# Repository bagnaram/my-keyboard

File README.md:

# Splendens

**75% keyboard with ISP programmer and USB-C**

**[LICENSE](LICENSE)**

<br />This work is licensed under a <a rel="license" href="http://creativecommons.org/licenses/by-sa/4.0/">Creative Commons Attribution-ShareAlike 4.0 International License</a>.

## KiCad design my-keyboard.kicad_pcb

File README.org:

#+TITLE: Ocotillo Keyboard

* KEYBOARD
60% keyboard with ISP programmer and USB-C

For details on construction please read the assembly blog
[[https://bagnaram.github.io/blog/2020/12/01/keyboard]]

* LICENSE
[[https://i.creativecommons.org/l/by-sa/4.0/88x31.png]]
[[http://creativecommons.org/licenses/by-sa/4.0/][Creative Commons Attribution-ShareAlike 4.0 International License]]

* PHOTOS
[[./doc/ocotillo.png]]
[[./doc/pcb.png]]
[[./doc/pcb-back.png]]

** BOM
I purchased everything from Mouser. Keep in mind these are all SMD components
except for the USB connector and fuse. Therefore, extra care is necessary to
ensure components are properly soldered. Small sensitive components such as the
crystal oscillator cannot endure high temperature of a standard iron. Proceed
with caution.

| Reference                                                                                                                                                                                                                                                                | Quantity | Value                    | Footprint                                      | Datasheet                                                                                                                     | SKU                                       | Quoted Part Number   | Order Quantity | Order Price | Min\Mult Order Qty |
| C1 C2 C3                                                                                                                                                                                                                                                                 |        3 | 0.1uF                    | Capacitor_SMD:C_0805_2012Metric                | Multilayer Ceramic Capacitors MLCC - SMD/SMT Multilayer Ceramic Capacitors MLCC - SMD/SMT .1uF 5% 25V MLCC                    | CC0805JPX7R8BB104                         | 603-CC0805JPX7R8BB10 |              3 | $0.18       | 1\1                |
| C4                                                                                                                                                                                                                                                                       |        1 | 10uF                     | Capacitor_SMD:C_0805_2012Metric                | Multilayer Ceramic Capacitors MLCC - SMD/SMT Multilayer Ceramic Capacitors MLCC - SMD/SMT 0805 25VDC 10uF 10% AEC-Q200        | CGA4J1X7S1E106K125AC                      | 810-CGA4J1X7S1E106K1 |              1 | $0.58       | 1\1                |
| C5 C6                                                                                                                                                                                                                                                                    |        2 | 22pF                     | Capacitor_SMD:C_0805_2012Metric                | Multilayer Ceramic Capacitors MLCC - SMD/SMT Multilayer Ceramic Capacitors MLCC - SMD/SMT 25V 22pF C0G 0805 10% Flex AEC-Q200 | C0805X220K3GACAUTO                        | 80-C0805X220K3GAUTO  |              2 | $0.34       | 1\1                |
| C7                                                                                                                                                                                                                                                                       |        1 | 1uF                      | Capacitor_SMD:C_0805_2012Metric                | Multilayer Ceramic Capacitors MLCC - SMD/SMT Multilayer Ceramic Capacitors MLCC - SMD/SMT 10V 1uF X7R 0805 20% AEC-Q200       | C0805C105M8RACAUTO                        | 80-C0805C105M8RAUTO  |              1 | $0.31       | 1\1                |
| D1 D2 D4 D5 D6 D7 D8 D9 D10 D11 D13 D14 D15 D16 D17 D19 D20 D21 D22 D24 D25 D26 D27 D29 D30 D31 D32 D34 D35 D36 D37 D38 D40 D41 D42 D43 D45 D46 D47 D48 D50 D51 D52 D53 D55 D56 D57 D58 D59 D61 D62 D63 D64 D65 D67 D68 D69 D70 D73 D74 D76 D78 D79 D80 D81 D82 D85      |       67 | D_Small                  | Diode_SMD:D_SOD-123                            | Diodes - General Purpose, Power, Switching Diodes - General Purpose, Power, Switching 100V Io/150mA                           | 1N4148W-E3-08                             | 78-1N4148W-E3-08     |             67 | $0.15       | 1\1                |
| D86 D87                                                                                                                                                                                                                                                                  |        2 | 3.6V                     | Diode_SMD:D_SOD-123                            | Zener Diodes Zener Diodes 3.6V 500mW                                                                                          | MMSZ4685T1G                               | 863-MMSZ4685T1G      |              2 | $0.21       | 1\1                |
| F1                                                                                                                                                                                                                                                                       |        1 | 500mA                    | cftkb:polyfuse_5.1mm                           | Resettable Fuses - PPTC Resettable Fuses - PPTC 60v Max 40Amps Max Hold .50 Trip 1.00                                         | MF-R050                                   | 652-MFR050           |              1 | $0.34       | 1\1                |
| ISP1                                                                                                                                                                                                                                                                     |        1 | AVR-ISP-6                | cftkb:AVR_ICSP_3x2                             | Headers & Wire Housings Headers & Wire Housings 6P DR VRT UNSHRD HDR TIN OVER NICKEL                                          | 68602-406HLF                              | 649-68602-406HLF     |              1 | $0.24       | 1\1                |
| MX0 MX1 MX2 MX3 MX4 MX5 MX6 MX7 MX8 MX9 MX10 MX11 MX12 MX14 MX16 MX17 MX18 MX19 MX20 MX21 MX22 MX23 MX24 MX25 MX26 MX27 MX29 MX31 MX32 MX33 MX34 MX35 MX36 MX37 MX38 MX39 MX40 MX41 MX43 MX45 MX46 MX47 MX48 MX49 MX50 MX51 MX52 MX53 MX54 MX56 MX57 MX63 MX64 MX65 MX66 |       55 | 1                        | MX_Alps_Hybrid:MX-1U-NoLED                     |                                                                                                                               | PCB Mount Gateron Switches (5 Legs) Brown |                      |                |             |                    |
| MX13                                                                                                                                                                                                                                                                     |        1 | 1                        | MX_Alps_Hybrid:MX-2U-NoLED                     |                                                                                                                               | PCB Mount Gateron Switches (5 Legs) Brown |                      |                |             |                    |
| MX15 MX28                                                                                                                                                                                                                                                                |        2 | 1                        | MX_Alps_Hybrid:MX-1.5U-NoLED                   |                                                                                                                               | PCB Mount Gateron Switches (5 Legs) Brown |                      |                |             |                    |
| MX30                                                                                                                                                                                                                                                                     |        1 | 1                        | MX_Alps_Hybrid:MX-1.75U                        |                                                                                                                               | PCB Mount Gateron Switches (5 Legs) Brown |                      |                |             |                    |
| MX42 MX44                                                                                                                                                                                                                                                                |        2 | 1                        | MX_Alps_Hybrid:MX-2.25U-NoLED                  |                                                                                                                               | PCB Mount Gateron Switches (5 Legs) Brown |                      |                |             |                    |
| MX55                                                                                                                                                                                                                                                                     |        1 | 1                        | MX_Alps_Hybrid:MX-1.75U-NoLED                  |                                                                                                                               | PCB Mount Gateron Switches (5 Legs) Brown |                      |                |             |                    |
| MX58 MX59 MX60 MX62                                                                                                                                                                                                                                                      |        4 | 1                        | MX_Alps_Hybrid:MX-1.25U-NoLED                  |                                                                                                                               | PCB Mount Gateron Switches (5 Legs) Brown |                      |                |             |                    |
| MX61                                                                                                                                                                                                                                                                     |        1 | 1                        | MX_Alps_Hybrid:MX-6U-ReversedStabilizers-NoLED |                                                                                                                               | PCB Mount Gateron Switches (5 Legs) Brown |                      |                |             |                    |
| R1 R2                                                                                                                                                                                                                                                                    |        2 | 75                       | Resistor_SMD:R_0805_2012Metric                 | Thick Film Resistors - SMD Thick Film Resistors - SMD 1/8W 75 Ohm 1%                                                          | GWCR0805-75RFT5                           | 756-GWCR0805-75RFT5  |              2 | $0.10       | 1\1                |
| R3 R4                                                                                                                                                                                                                                                                    |        2 | 10k                      | Resistor_SMD:R_0805_2012Metric                 | Thick Film Resistors - SMD Thick Film Resistors - SMD 10K ohm 1% 150V General Purpose SMT                                     | WCR0805-10KFI                             | 756-WCR0805-10KFI    |              2 | $0.10       | 1\1                |
| R5 R6                                                                                                                                                                                                                                                                    |        2 | 5.1k                     | Resistor_SMD:R_0805_2012Metric                 | Thick Film Resistors - SMD Thick Film Resistors - SMD 5.1K 1%                                                                 | CR0805-FX-5101ELF                         | 652-CR0805FX-5101ELF |              2 | $0.10       | 1\1                |
| R7                                                                                                                                                                                                                                                                       |        1 | 1.5k                     | Resistor_SMD:R_0805_2012Metric                 | Thick Film Resistors - SMD Thick Film Resistors - SMD 1.5K 1%                                                                 | CR0805-FX-1501ELF                         | 652-CR0805FX-1501ELF |              1 | $0.10       | 1\1                |
| SW1                                                                                                                                                                                                                                                                      |        1 | SW_Push                  | Random Keyboard Parts:SKQGADE010               | Tactile Switches Tactile Switches 5.2x5.2x1.5mm 260gf                                                                         | SKQGADE010                                | 688-SKQGAD           |              1 | $0.46       | 1\1                |
| U1                                                                                                                                                                                                                                                                       |        1 | ATmega32U4-AU            | Package_QFP:TQFP-44_10x10mm_P0.8mm             | 8-bit Microcontrollers - MCU 8-bit Microcontrollers - MCU AVR USB 32K FLASH INDUSTRIAL                                        | ATmega32U4-AU                             | 556-ATMEGA32U4-AU    |              1 | $4.00       | 1\1                |
| USB1                                                                                                                                                                                                                                                                     |        1 | USB_C_GCT_USB4085-Type-C | cftkb:USB_C_GCT_USB4085                        | USB Connectors USB Connectors USB 3.1 RECE. CONN. Gen 1                                                                       | 10137061-00021LF                          | 649-10137061-00021LF |              1 | $2.24       | 1\1                |
| Y1                                                                                                                                                                                                                                                                       |        1 | 16MHz                    | Crystal:Crystal_SMD_3225-4Pin_3.2x2.5mm        | Crystals Crystals CRYSTAL 16MHZ 8PF SMD                                                                                       | NX3225GA-16.000M-STD-CRG-2                | 344-NX3225GA16MCRG2  |              1 | $0.59       | 1\1                |

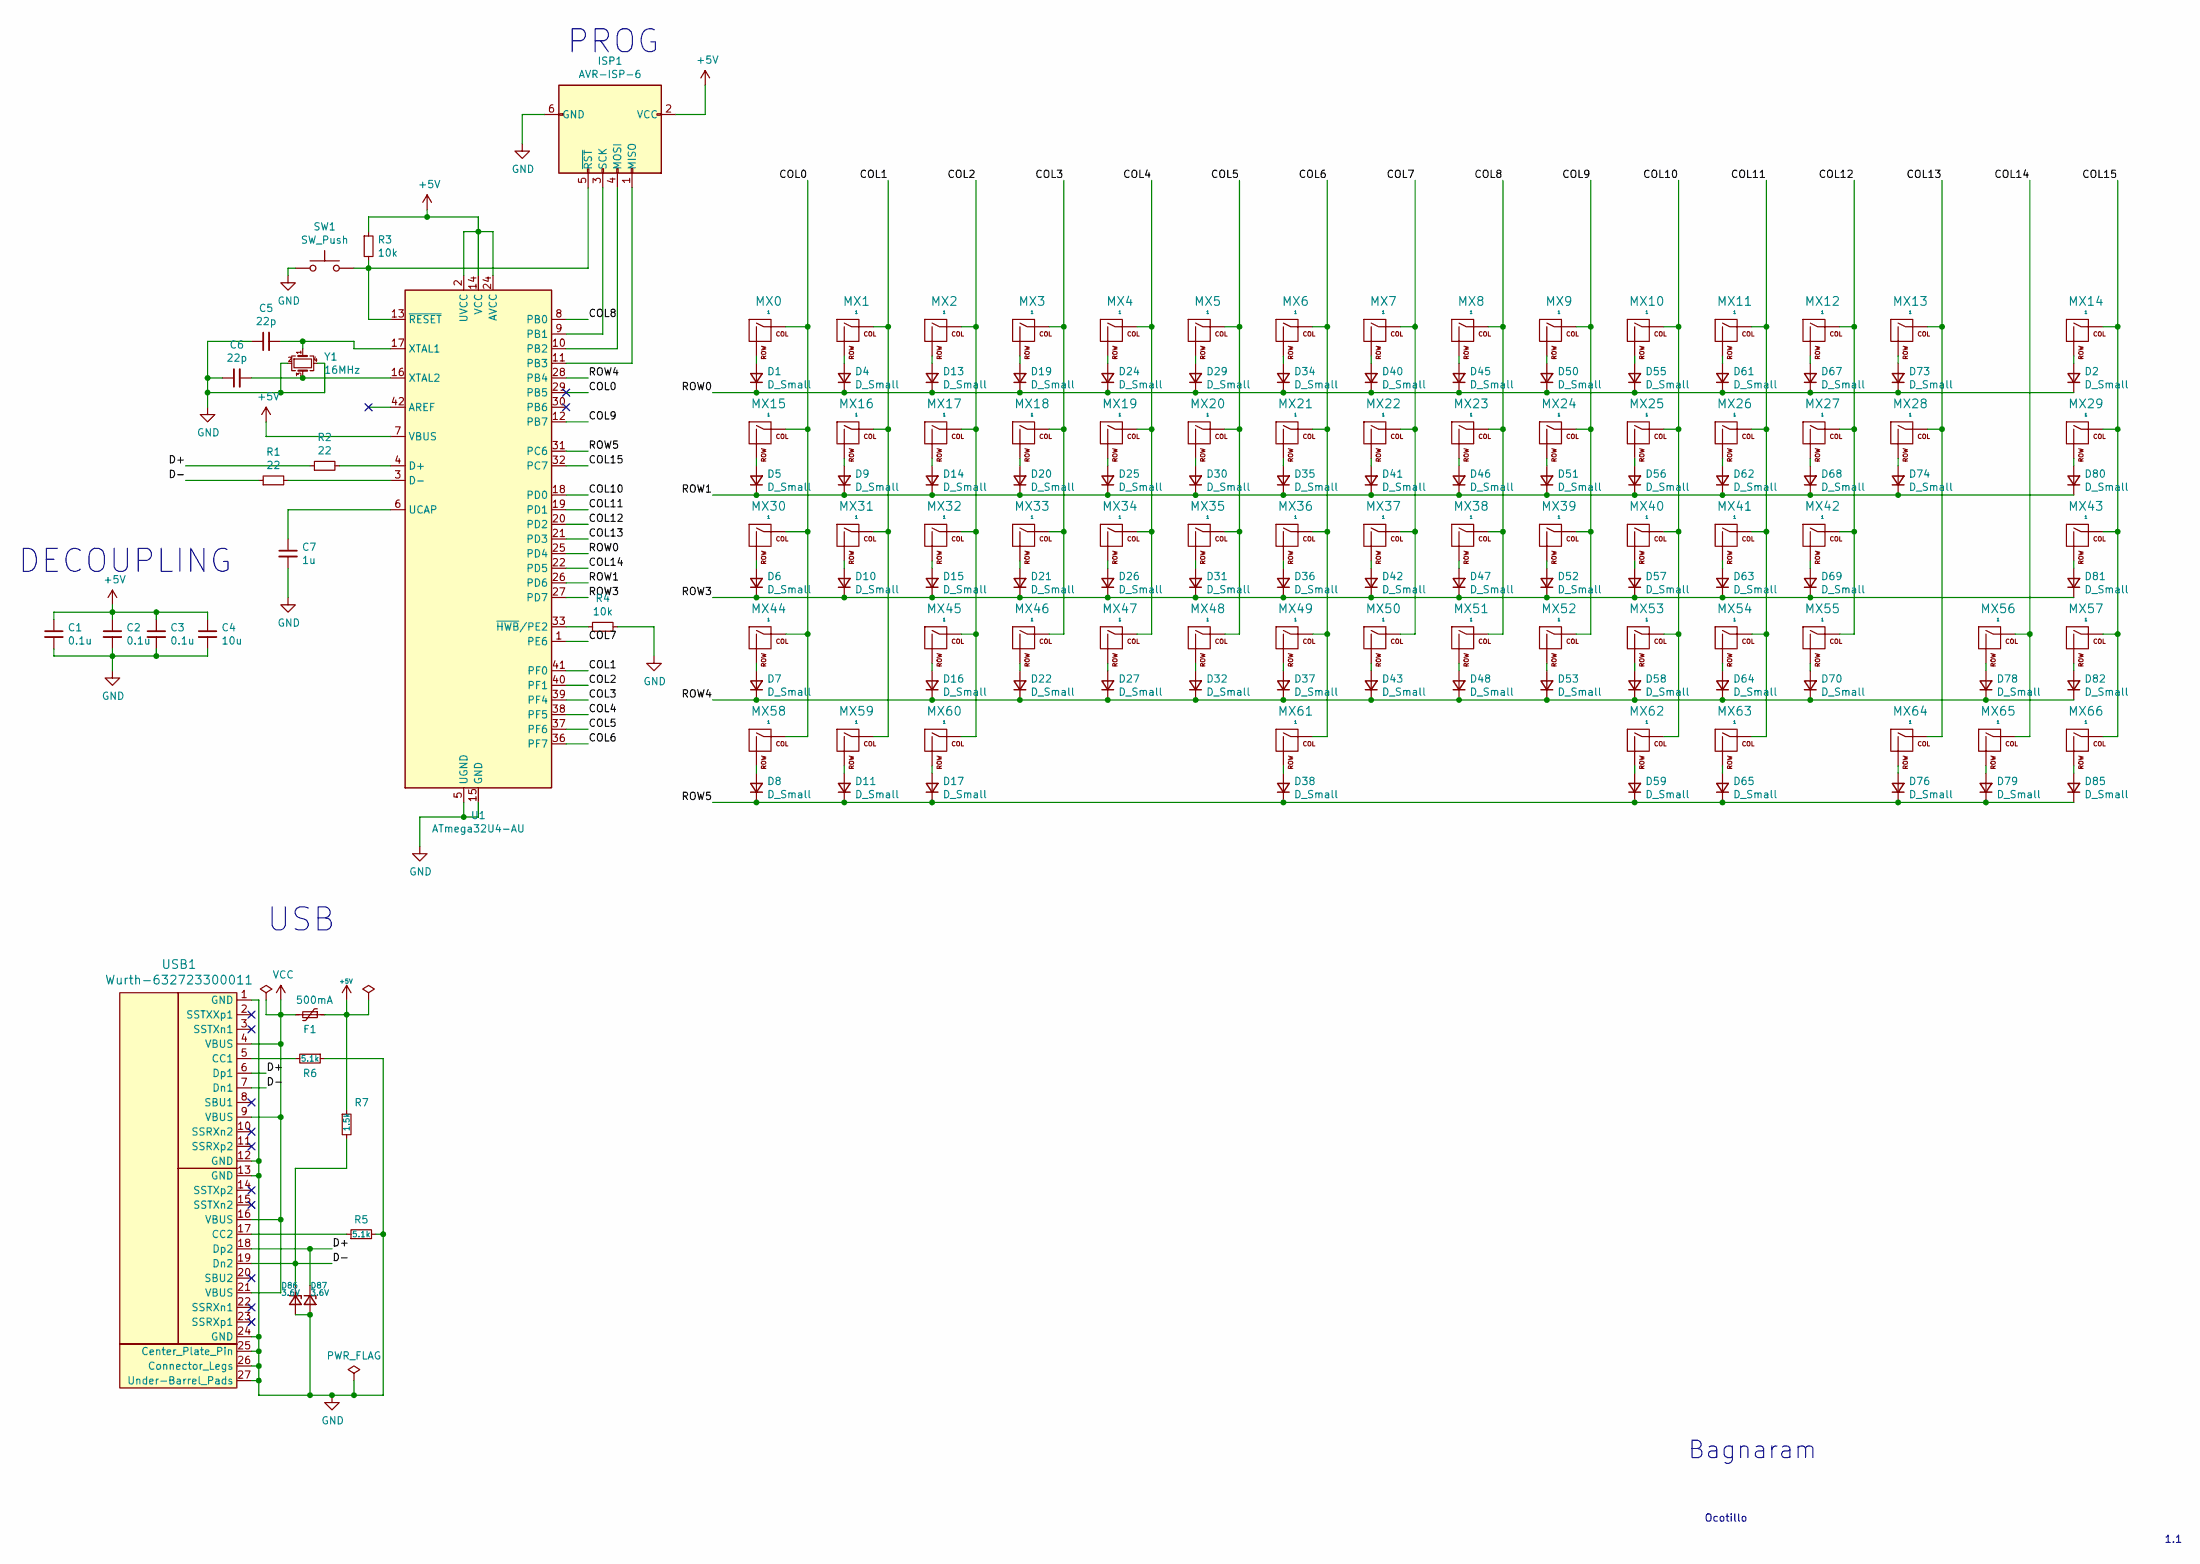
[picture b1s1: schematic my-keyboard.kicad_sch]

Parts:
C1, C2, C3: 0.1u; C_0805_2012Metric
C4: 10u; C_0805_2012Metric
C5, C6: 22p; C_0805_2012Metric
C7: 1u; C_0805_2012Metric
D1, D2, D4, D5, D6, D7, D8, D9, D10, D11, D13, D14, D15, D16, D17, D19, D20, D21, D22, D24, D25, D26, D27, D29, D30, D31, D32, D34, D35, D36, D37, D38, D40, D41, D42, D43, D45, D46, D47, D48, D50, D51, D52, D53, D55, D56, D57, D58, D59, D61, D62, D63, D64, D65, D67, D68, D69, D70, D73, D74, D76, D78, D79, D80, D81, D82, D85: D_Small; D_SOD-123
D86, D87: 3.6V; D_SOD-123
F1: 500mA; polyfuse_5.1mm
ISP1: AVR-ISP-6; AVR_ICSP_3x2
MX0, MX1, MX2, MX3, MX4, MX5, MX6, MX7, MX8, MX9, MX10, MX11, MX12, MX14, MX16, MX17, MX18, MX19, MX20, MX21, MX22, MX23, MX24, MX25, MX26, MX27, MX29, MX31, MX32, MX33, MX34, MX35, MX36, MX37, MX38, MX39, MX40, MX41, MX43, MX45, MX46, MX47, MX48, MX49, MX50, MX51, MX52, MX53, MX54, MX56, MX57, MX63, MX64, MX65, MX66: 1; MX-1U-NoLED
MX13: 1; MX-2U-NoLED
MX15, MX28: 1; MX-1.5U-NoLED
MX30: 1; MX-1.75U
MX42, MX44: 1; MX-2.25U-NoLED
MX55: 1; MX-1.75U-NoLED
MX58, MX59, MX60, MX62: 1; MX-1.25U-NoLED
MX61: 1; MX-6U-ReversedStabilizers-NoLED
R1, R2: 22; R_0805_2012Metric
R3, R4: 10k; R_0805_2012Metric
R5, R6: 5.1k; R_0805_2012Metric
R7: 1.5k; R_0805_2012Metric
SW1: SW_Push; SKQGADE010
U1: ATmega32U4-AU; TQFP-44_10x10mm_P0.8mm
USB1: Wurth-632723300011
Y1: 16MHz; Crystal_SMD_3225-4Pin_3.2x2.5mm

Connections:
+5V: C1.1, C2.1, C3.1, C4.1, F1.1, ISP1.2 (VCC), R3.1, R7.1, U1.2 (UVCC), U1.7 (VBUS), U1.14 (VCC), U1.24 (AVCC), U1.34 (VCC), U1.44 (AVCC)
/COL0: MX0.1 (COL), MX15.1 (COL), MX30.1 (COL), MX44.1 (COL), MX58.1 (COL), U1.29 (PB5)
/COL1: MX1.1 (COL), MX16.1 (COL), MX31.1 (COL), MX59.1 (COL), U1.41 (PF0)
/COL2: MX2.1 (COL), MX17.1 (COL), MX32.1 (COL), MX45.1 (COL), MX60.1 (COL), U1.40 (PF1)
/COL3: MX3.1 (COL), MX18.1 (COL), MX33.1 (COL), MX46.1 (COL), U1.39 (PF4)
/COL4: MX4.1 (COL), MX19.1 (COL), MX34.1 (COL), MX47.1 (COL), U1.38 (PF5)
/COL5: MX5.1 (COL), MX20.1 (COL), MX35.1 (COL), MX48.1 (COL), U1.37 (PF6)
/COL6: MX6.1 (COL), MX21.1 (COL), MX36.1 (COL), MX49.1 (COL), MX61.1 (COL), U1.36 (PF7)
/COL7: MX7.1 (COL), MX22.1 (COL), MX37.1 (COL), MX50.1 (COL), U1.1 (PE6)
/COL8: MX8.1 (COL), MX23.1 (COL), MX38.1 (COL), MX51.1 (COL), U1.8 (PB0)
/COL9: MX9.1 (COL), MX24.1 (COL), MX39.1 (COL), MX52.1 (COL), U1.12 (PB7)
/COL10: MX10.1 (COL), MX25.1 (COL), MX40.1 (COL), MX53.1 (COL), MX62.1 (COL), U1.18 (PD0)
/COL11: MX11.1 (COL), MX26.1 (COL), MX41.1 (COL), MX54.1 (COL), MX63.1 (COL), U1.19 (PD1)
/COL12: MX12.1 (COL), MX27.1 (COL), MX42.1 (COL), MX55.1 (COL), U1.20 (PD2)
/COL13: MX13.1 (COL), MX28.1 (COL), MX64.1 (COL), U1.21 (PD3)
/COL14: MX56.1 (COL), MX65.1 (COL), U1.22 (PD5)
/COL15: MX14.1 (COL), MX29.1 (COL), MX43.1 (COL), MX57.1 (COL), MX66.1 (COL), U1.32 (PC7)
/D+: D87.1 (K), R2.1, USB1.6 (Dp1), USB1.18 (Dp2)
/D-: D86.1 (K), R1.1, R7.2, USB1.7 (Dn1), USB1.19 (Dn2)
/ROW0: D1.1 (K), D2.1 (K), D4.1 (K), D13.1 (K), D19.1 (K), D24.1 (K), D29.1 (K), D34.1 (K), D40.1 (K), D45.1 (K), D50.1 (K), D55.1 (K), D61.1 (K), D67.1 (K), D73.1 (K), U1.25 (PD4)
/ROW1: D5.1 (K), D9.1 (K), D14.1 (K), D20.1 (K), D25.1 (K), D30.1 (K), D35.1 (K), D41.1 (K), D46.1 (K), D51.1 (K), D56.1 (K), D62.1 (K), D68.1 (K), D74.1 (K), D80.1 (K), U1.26 (PD6)
/ROW3: D6.1 (K), D10.1 (K), D15.1 (K), D21.1 (K), D26.1 (K), D31.1 (K), D36.1 (K), D42.1 (K), D47.1 (K), D52.1 (K), D57.1 (K), D63.1 (K), D69.1 (K), D81.1 (K), U1.27 (PD7)
/ROW4: D7.1 (K), D16.1 (K), D22.1 (K), D27.1 (K), D32.1 (K), D37.1 (K), D43.1 (K), D48.1 (K), D53.1 (K), D58.1 (K), D64.1 (K), D70.1 (K), D78.1 (K), D82.1 (K), U1.28 (PB4)
/ROW5: D8.1 (K), D11.1 (K), D17.1 (K), D38.1 (K), D59.1 (K), D65.1 (K), D76.1 (K), D79.1 (K), D85.1 (K), U1.31 (PC6)
GND: C1.2, C2.2, C3.2, C4.2, C5.1, C6.1, C7.2, D86.2 (A), D87.2 (A), ISP1.6 (GND), R4.2, R5.2, R6.1, SW1.1, U1.5 (UGND), U1.15 (GND), U1.23 (GND), U1.35 (GND), U1.43 (GND), USB1.1 (GND), USB1.12 (GND), USB1.13 (GND), USB1.24 (GND), USB1.25 (Center_Plate_Pin), USB1.26 (Connector_Legs), USB1.27 (Under-Barrel_Pads), Y1.2, Y1.4
unnamed: C5.2, U1.17 (XTAL1), Y1.1
unnamed: C6.2, U1.16 (XTAL2), Y1.3
unnamed: C7.1, U1.6 (UCAP)
unnamed: D1.2 (A), MX0.2 (ROW)
unnamed: D2.2 (A), MX14.2 (ROW)
unnamed: D4.2 (A), MX1.2 (ROW)
unnamed: D5.2 (A), MX15.2 (ROW)
unnamed: D6.2 (A), MX30.2 (ROW)
unnamed: D7.2 (A), MX44.2 (ROW)
unnamed: D8.2 (A), MX58.2 (ROW)
unnamed: D9.2 (A), MX16.2 (ROW)
unnamed: D10.2 (A), MX31.2 (ROW)
unnamed: D11.2 (A), MX59.2 (ROW)
unnamed: D13.2 (A), MX2.2 (ROW)
unnamed: D14.2 (A), MX17.2 (ROW)
unnamed: D15.2 (A), MX32.2 (ROW)
unnamed: D16.2 (A), MX45.2 (ROW)
unnamed: D17.2 (A), MX60.2 (ROW)
unnamed: D19.2 (A), MX3.2 (ROW)
unnamed: D20.2 (A), MX18.2 (ROW)
unnamed: D21.2 (A), MX33.2 (ROW)
unnamed: D22.2 (A), MX46.2 (ROW)
unnamed: D24.2 (A), MX4.2 (ROW)
unnamed: D25.2 (A), MX19.2 (ROW)
unnamed: D26.2 (A), MX34.2 (ROW)
unnamed: D27.2 (A), MX47.2 (ROW)
unnamed: D29.2 (A), MX5.2 (ROW)
unnamed: D30.2 (A), MX20.2 (ROW)
unnamed: D31.2 (A), MX35.2 (ROW)
unnamed: D32.2 (A), MX48.2 (ROW)
unnamed: D34.2 (A), MX6.2 (ROW)
unnamed: D35.2 (A), MX21.2 (ROW)
unnamed: D36.2 (A), MX36.2 (ROW)
unnamed: D37.2 (A), MX49.2 (ROW)
unnamed: D38.2 (A), MX61.2 (ROW)
unnamed: D40.2 (A), MX7.2 (ROW)
unnamed: D41.2 (A), MX22.2 (ROW)
unnamed: D42.2 (A), MX37.2 (ROW)
unnamed: D43.2 (A), MX50.2 (ROW)
unnamed: D45.2 (A), MX8.2 (ROW)
unnamed: D46.2 (A), MX23.2 (ROW)
unnamed: D47.2 (A), MX38.2 (ROW)
unnamed: D48.2 (A), MX51.2 (ROW)
unnamed: D50.2 (A), MX9.2 (ROW)
unnamed: D51.2 (A), MX24.2 (ROW)
unnamed: D52.2 (A), MX39.2 (ROW)
unnamed: D53.2 (A), MX52.2 (ROW)
unnamed: D55.2 (A), MX10.2 (ROW)
unnamed: D56.2 (A), MX25.2 (ROW)
unnamed: D57.2 (A), MX40.2 (ROW)
unnamed: D58.2 (A), MX53.2 (ROW)
unnamed: D59.2 (A), MX62.2 (ROW)
unnamed: D61.2 (A), MX11.2 (ROW)
unnamed: D62.2 (A), MX26.2 (ROW)
unnamed: D63.2 (A), MX41.2 (ROW)
unnamed: D64.2 (A), MX54.2 (ROW)
unnamed: D65.2 (A), MX63.2 (ROW)
unnamed: D67.2 (A), MX12.2 (ROW)
unnamed: D68.2 (A), MX27.2 (ROW)
unnamed: D69.2 (A), MX42.2 (ROW)
unnamed: D70.2 (A), MX55.2 (ROW)
unnamed: D73.2 (A), MX13.2 (ROW)
unnamed: D74.2 (A), MX28.2 (ROW)
unnamed: D76.2 (A), MX64.2 (ROW)
unnamed: D78.2 (A), MX56.2 (ROW)
unnamed: D79.2 (A), MX65.2 (ROW)
unnamed: D80.2 (A), MX29.2 (ROW)
unnamed: D81.2 (A), MX43.2 (ROW)
unnamed: D82.2 (A), MX57.2 (ROW)
unnamed: D85.2 (A), MX66.2 (ROW)
unnamed: ISP1.1 (MISO), U1.11 (PB3)
unnamed: ISP1.3 (SCK), U1.9 (PB1)
unnamed: ISP1.4 (MOSI), U1.10 (PB2)
unnamed: ISP1.5 (~RST), R3.2, SW1.2, U1.13 (~RESET)
unnamed: R1.2, U1.3 (D-)
unnamed: R2.2, U1.4 (D+)
unnamed: R4.1, U1.33 (~HWB~/PE2)
unnamed: R5.1, USB1.17 (CC2)
unnamed: R6.2, USB1.5 (CC1)
VCC: F1.2, USB1.4 (VBUS), USB1.9 (VBUS), USB1.16 (VBUS), USB1.21 (VBUS)

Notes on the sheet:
DECOUPLING
USB
PROG
Ocotillo
Bagnaram
1.1

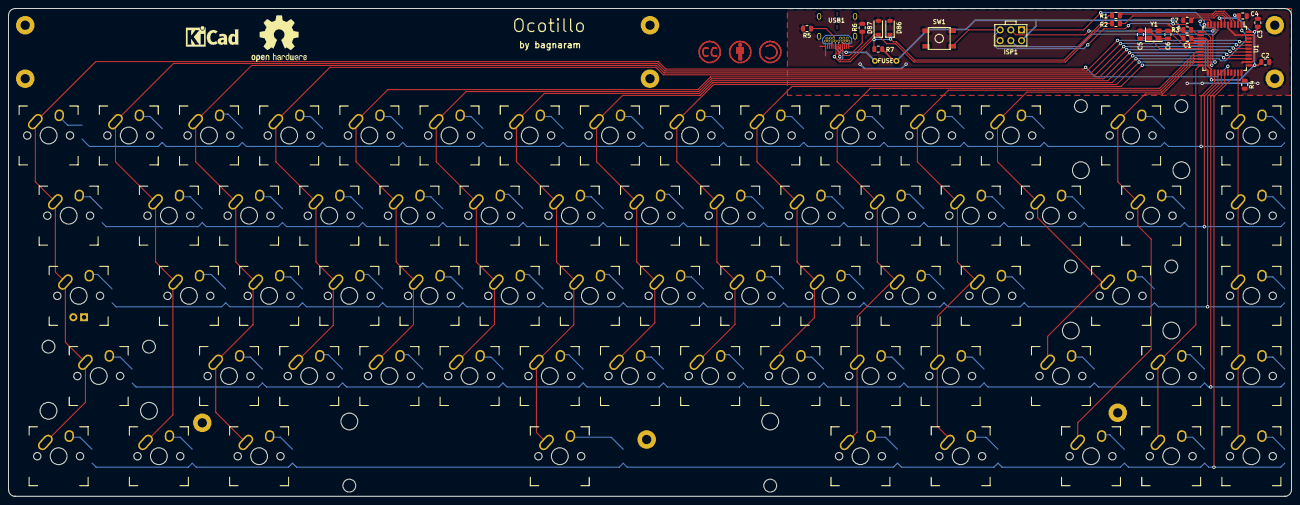
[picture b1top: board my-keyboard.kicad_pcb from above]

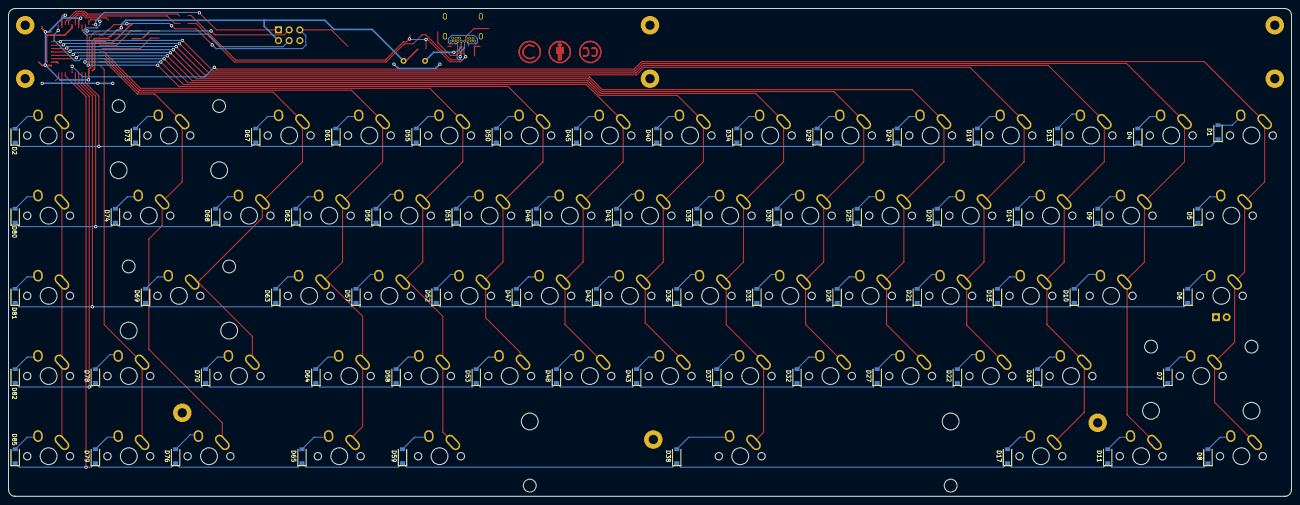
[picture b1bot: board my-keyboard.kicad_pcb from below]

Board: 2 copper layers, 304.8 x 115.9 mm, 161 parts (67 on the bottom side), 105 nets.

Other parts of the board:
SYM1: Symbol_CreativeCommons_CopperTop_Type2_Small
SYM2: Symbol_CC-Attribution_CopperTop_Small
SYM3: Symbol_CC-ShareAlike_CopperTop_Small
SYM4: OSHW-Logo2_14.6x12mm_SilkScreen
SYM5: KiCad-Logo_5mm_SilkScreen

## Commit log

2020-03-29 added submodules
2020-03-29 set up schematic libraries
2020-03-30 pcb footprints
2020-04-06 Day 3 commit
2020-04-06 add license
2020-05-04 wires and pcb
2020-07-12 Add gerbers
2020-07-12 refresh gerbers
2020-09-24 Redesign keyboard with %75 keys
2020-10-03 optimizations, footprint change
2020-10-03 gitignore
2020-10-03 remove gitignore files
2020-10-03 README
2020-10-03 images
2020-10-03 image and fixup
2020-10-03 kb image
2020-10-03 pcb image
2020-10-04 cleanup
2020-10-05 different usb footprint
2020-10-31 Generated gerbers
2020-11-17 fix aref pin
2020-12-07 rev 1.1
2020-12-13 org table
2020-12-13 format and link
